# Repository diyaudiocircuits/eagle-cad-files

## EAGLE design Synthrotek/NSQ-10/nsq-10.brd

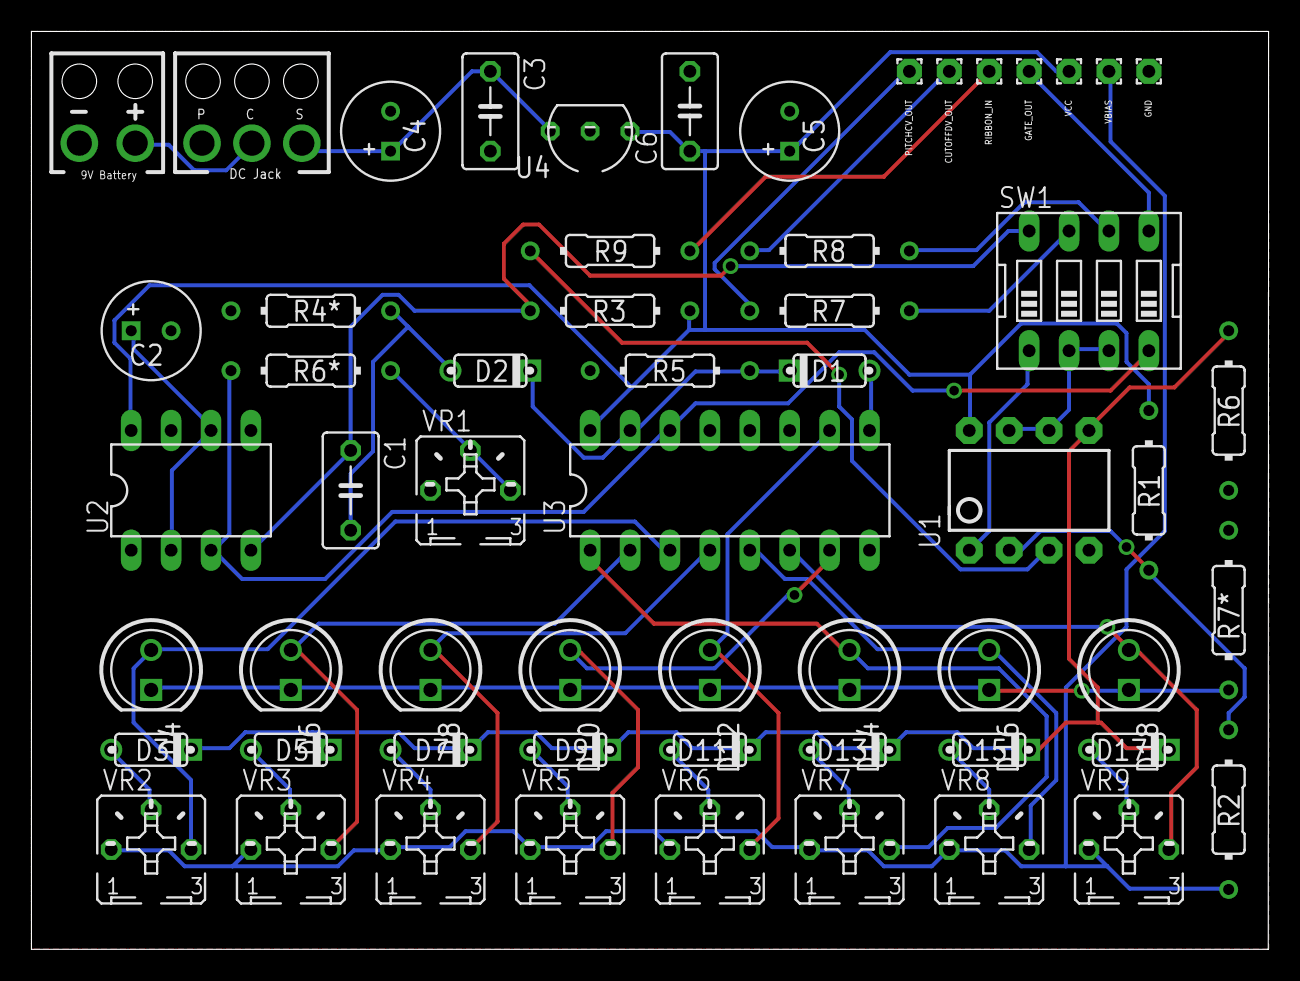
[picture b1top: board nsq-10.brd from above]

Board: 2 copper layers, 78.7 x 58.4 mm, 58 parts (0 on the bottom side), 40 nets.

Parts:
C1: 0.001uF; CERAMIC_CAP
C2: 0.47uF; 063_025
C3, C6: 0.1uF; CERAMIC_CAP
C4: 100uF; 063_025
C5: 10uF; 063_025
CUTOFFDV_OUT: 1,6/0,8
D1, D2: 1N914.2; DO35-2
D3, D5, D7, D9, D11, D13, D15, D17: 1N4148; DO35-2
D4, D6, D8, D10, D12, D14, D16, D18: LED5MM
GATE_OUT: 1,6/0,8
GND: 1,6/0,8
PITCHCV_OUT: 1,6/0,8
R1, R3, R4*, R5: 100k; RESISTOR
R2: 2.2k; RESISTOR
R6, R7*: 10k; RESISTOR
R6*: 20k; RESISTOR
R7: 91K; RESISTOR
R8: 470k; RESISTOR
R9: 1k; RESISTOR
RIBBON_IN: 1,6/0,8
SW1: EDG-04
U1: LM358; DIP08
U2: ICM7555; DIL08
U3: 4017N; DIL16
U4: 78L05ACZ; TO-92
U$1: 9V_BATTERY_CLIP; 9V_BATTERY
U$2: DC_JACK_OFFBOARD
VBIAS: 1,6/0,8
VCC: 1,6/0,8
VR1: 1M; B25P
VR2, VR3, VR4, VR5, VR6, VR7, VR8, VR9: 10k; B25P

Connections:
CLOCK: R6*.1, SW1.4, U2.3, U3.14
CUTOFFCV_B: R8.2, SW1.6
GATE_B: GATE_OUT.1, SW1.5
GND: C2.-, C3.2, C4.-, C5.-, C6.2, GND.1, R4*.1, R5.1, R6.1, R7*.1, U1.4, U2.1, U3.8, U3.13, U4.2, U$1.9V_BATTERY_-, U$2.PIN, VR1.A
unnamed: C1.2, D2.A, R4*.2
unnamed: R1.1, R2.2, U1.2
unnamed: R6*.2, VR1.E, VR1.S
unnamed: C2.+, U2.2, U2.6
unnamed: SW1.2, SW1.3, U1.6, U1.7
unnamed: D3.A, VR2.S
unnamed: R9.1, RIBBON_IN.1
unnamed: D5.A, VR3.S
unnamed: D1.A, U3.9
unnamed: D1.C, D2.C, R5.2, U3.15
unnamed: CUTOFFDV_OUT.1, R8.1
unnamed: D7.A, VR4.S
unnamed: PITCHCV_OUT.1, R7.1
unnamed: D9.A, VR5.S
unnamed: D11.A, VR6.S
unnamed: D13.A, VR7.S
unnamed: U$1.9V_BATTERY_+, U$2.CONNECT
unnamed: D15.A, VR8.S
unnamed: C3.1, C4.+, U4.3, U$2.SLEEVE
unnamed: D17.A, VR9.S
unnamed: D4.K, D6.K, D8.K, D10.K, D12.K, D14.K, D16.K, D18.K, R7*.2
unnamed: D3.C, D5.C, D7.C, D9.C, D11.C, D13.C, D15.C, D17.C, R6.2, U1.5
PITCHCV_B: R7.2, SW1.7
Q0: D4.A, U3.3, VR2.E
Q1: D6.A, U3.2, VR3.E
Q2: D8.A, U3.4, VR4.E
Q3: D10.A, U3.7, VR5.E
Q4: D12.A, U3.10, VR6.E
Q5: D14.A, U3.1, VR7.E
Q6: D16.A, U3.5, VR8.E
Q7: D18.A, U3.6, VR9.E
RESETMODE_A: SW1.1, U1.1
RESETMODE_B: C1.1, R3.1, SW1.8, U2.4
RIBBON_IN: R9.2, U1.3
VBIAS: R2.1, VBIAS.1, VR2.A, VR3.A, VR4.A, VR5.A, VR6.A, VR7.A, VR8.A, VR9.A
VCC: C5.+, C6.1, R1.2, R3.2, U1.8, U2.8, U3.16, U4.1, VCC.1

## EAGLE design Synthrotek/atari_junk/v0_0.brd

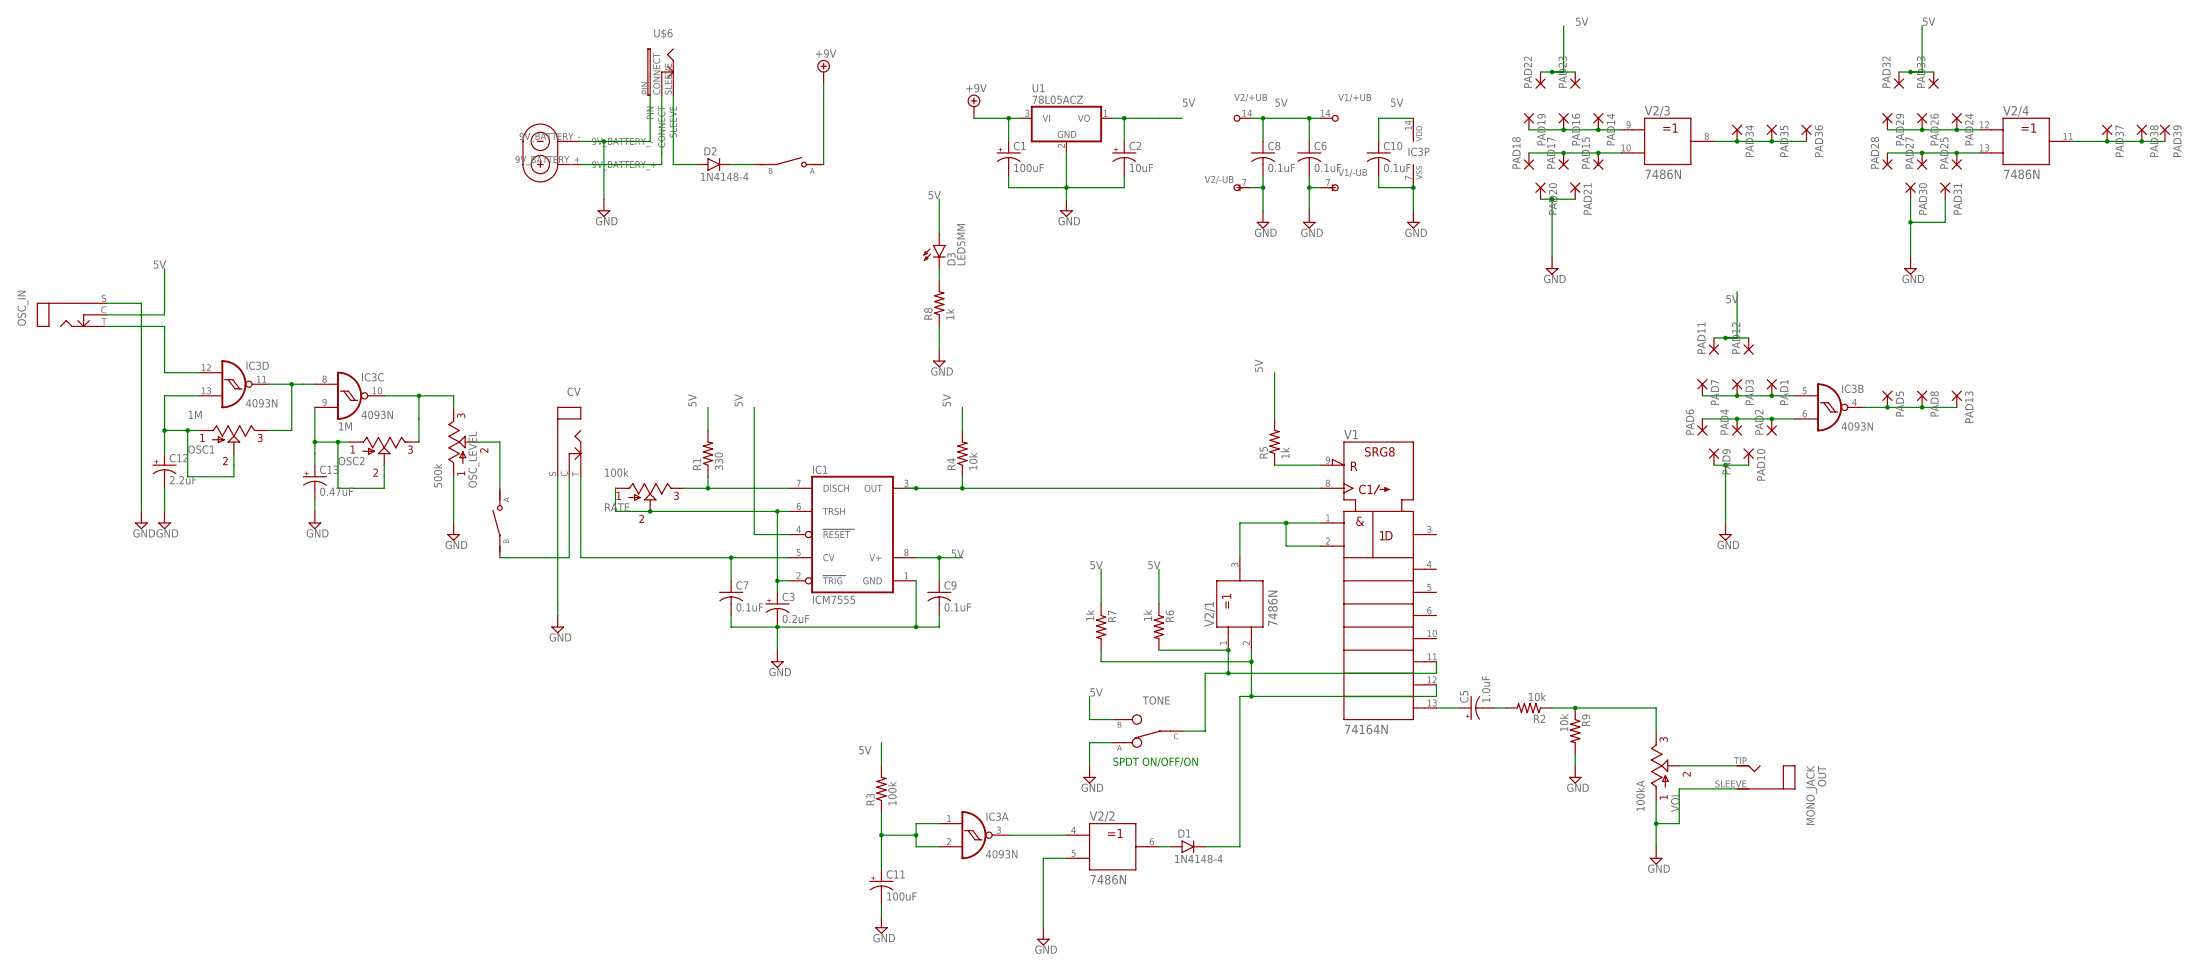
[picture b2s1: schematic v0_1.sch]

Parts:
C1, C11: 100uF; 063_025
C2: 10uF; 063_025
C3: 0.2uF; 063_025
C5: 1.0uF; 063_025
C6, C7, C8, C9, C10: 0.1uF; C050-030X075
C12: 2.2uF; 063_025
C13: 0.47uF; 063_025
CV: MONO_JACK_W_SHUNT
CV+OSC_ON/OFF: SPST_SWITCH; SPST_TOGGLE_SWITCH
D1, D2: 1N4148-4; DO35-4
D3: LED5MM
IC1: ICM7555; DIL08
IC3: 4093N; DIL14
ON/OFF: SPST_SWITCH; SPST_TOGGLE_SWITCH
OSC1, OSC2: 1M; POT
OSC_IN: MONO_JACK_W_SHUNT
OSC_LEVEL: 500k; POT
OUT: MONO_JACK
PAD1, PAD2, PAD3, PAD4, PAD5, PAD6, PAD7, PAD8, PAD9, PAD10, PAD11, PAD12, PAD13, PAD14, PAD15, PAD16, PAD17, PAD18, PAD19, PAD20, PAD21, PAD22, PAD23, PAD24, PAD25, PAD26, PAD27, PAD28, PAD29, PAD30, PAD31, PAD32, PAD33, PAD34, PAD35, PAD36, PAD37, PAD38, PAD39: WIREPAD1,6/0,9; 1,6/0,9
R1: 330; R0207/4
R2, R4, R9: 10k; R0207/4
R3: 100k; R0207/4
R5, R6, R7, R8: 1k; R0207/4
RATE: 100k; POT
TONE: SPDT_SWITCH; SPDT_TOGGLE_SWITCH
U1: 78L05ACZ; TO-92
U$6: DC_JACK_OFFBOARD
U$7: 9V_BATTERY_CLIP; 9V_BATTERY
V1: 74164N; DIL14
V2: 7486N; DIL14
VOL: 100kA; POT

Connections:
5V: C2.+, C6.1, C8.1, C9.1, C10.1, D3.A, IC1.4 (RESET), IC1.8 (V+), IC3.14 (VDD), OSC_IN.C (CONNECT), PAD11.1, PAD12.1, PAD22.1, PAD23.1, PAD32.1, PAD33.1, R1.2, R3.2, R4.2, R5.2, R6.1, R7.1, TONE.B, U1.1 (VO), V1.14 (+UB), V2.14 (+UB)
+9V: C1.+, ON/OFF.A, U1.3 (VI)
GND: C1.-, C2.-, C3.-, C6.2, C7.2, C8.2, C9.2, C10.2, C11.-, C12.-, C13.-, CV.S (SLEEVE), IC1.1 (GND), IC3.7 (VSS), OSC_IN.S (SLEEVE), OSC_LEVEL.1, OUT.SLEEVE, PAD9.1, PAD10.1, PAD20.1, PAD21.1, PAD30.1, PAD31.1, R8.1, R9.2, TONE.A, U1.2 (GND), U$6.PIN, U$7.9V_BATTERY_-, V1.7 (-UB), V2.5 (B), V2.7 (-UB), VOL.1
unnamed: C3.+, IC1.2 (TRIG), IC1.6 (TRSH), RATE.1, RATE.2
unnamed: U$6.CONNECT, U$7.9V_BATTERY_+
unnamed: IC1.3 (OUT), R4.1, V1.8 (CLK)
unnamed: IC1.7 (DISCH), R1.1, RATE.3
unnamed: R5.1, V1.9 (!CLR)
unnamed: PAD15.1, PAD17.1, PAD18.1, V2.10 (B)
unnamed: C7.1, CV.T (TIP), IC1.5 (CV)
unnamed: V1.1 (A), V1.2 (B), V2.3 (Y)
unnamed: R6.2, TONE.C, V1.11 (QF), V2.1 (A)
unnamed: D1.C, R7.2, V1.12 (QG), V2.2 (B)
unnamed: C5.+, V1.13 (QH)
unnamed: C5.-, R2.2
unnamed: R2.1, R9.1, VOL.3
unnamed: OUT.TIP, VOL.2
unnamed: IC3.12 (I0), OSC_IN.T (TIP)
unnamed: C12.+, IC3.13 (I1), OSC1.1, OSC1.2
unnamed: CV.C (CONNECT), CV+OSC_ON/OFF.B
unnamed: C11.+, IC3.1 (I0), IC3.2 (I1), R3.1
unnamed: IC3.3 (O), V2.4 (A)
unnamed: D1.A, V2.6 (Y)
unnamed: IC3.8 (I0), IC3.11 (O), OSC1.3
unnamed: D3.K (C), R8.2
unnamed: PAD14.1, PAD16.1, PAD19.1, V2.9 (A)
unnamed: IC3.4 (O), PAD5.1, PAD8.1, PAD13.1
unnamed: IC3.6 (I1), PAD2.1, PAD4.1, PAD6.1
unnamed: IC3.5 (I0), PAD1.1, PAD3.1, PAD7.1
unnamed: PAD34.1, PAD35.1, PAD36.1, V2.8 (Y)
unnamed: PAD37.1, PAD38.1, PAD39.1, V2.11 (Y)
unnamed: PAD25.1, PAD27.1, PAD28.1, V2.13 (B)
unnamed: PAD24.1, PAD26.1, PAD29.1, V2.12 (A)
unnamed: CV+OSC_ON/OFF.A, OSC_LEVEL.2
unnamed: C13.+, IC3.9 (I1), OSC2.1, OSC2.2
unnamed: D2.A, U$6.SLEEVE
unnamed: D2.C, ON/OFF.B
unnamed: IC3.10 (O), OSC2.3, OSC_LEVEL.3

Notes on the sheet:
SPDT ON/OFF/ON

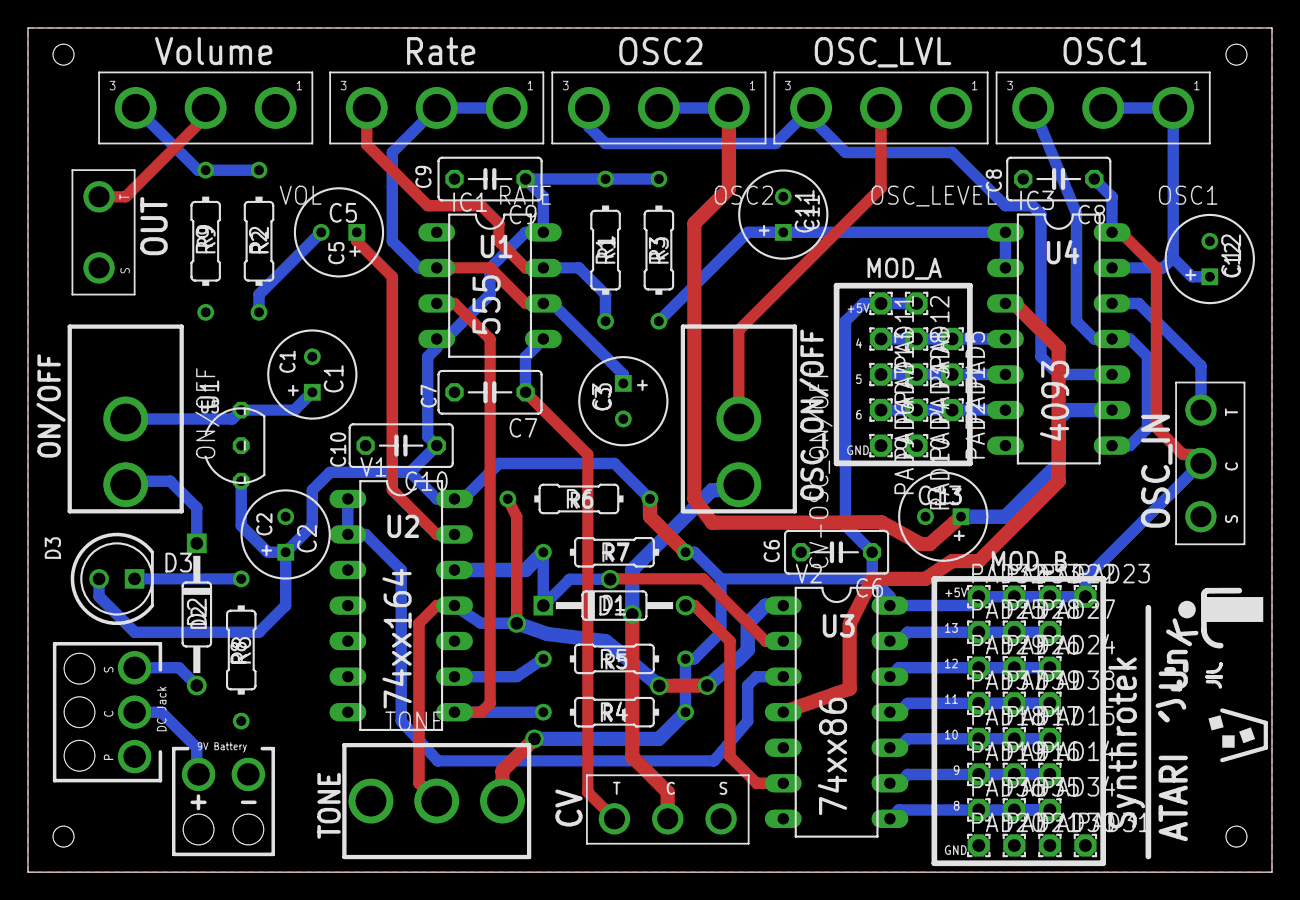
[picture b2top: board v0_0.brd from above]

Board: 2 copper layers, 88.9 x 60.3 mm, 81 parts (0 on the bottom side), 38 nets.

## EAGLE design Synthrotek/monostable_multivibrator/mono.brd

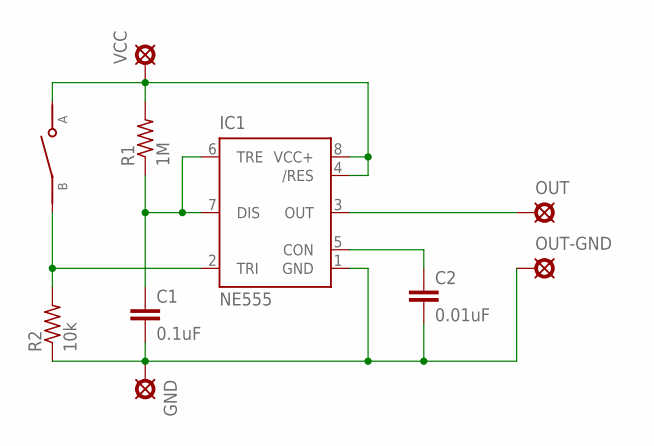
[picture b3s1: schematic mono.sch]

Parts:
C1: 0.1uF; 050X030_025
C2: 0.01uF; 050X030_025
GND: PAD8; OCTOGON
IC1: NE555; DIL-08
OUT: PAD; SQUARE
OUT-GND: PAD; SQUARE
R1: 1M; R0207/4
R2: 10k; R0207/4
SW1: SPST_SWITCH; SPST_TOGGLE_SWITCH
VCC: PAD; SQUARE

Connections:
unnamed: C1.1, IC1.6 (TRE), IC1.7 (DIS), R1.1
unnamed: IC1.3 (OUT), OUT.1
unnamed: IC1.4 (/RES), IC1.8 (VCC+), R1.2, SW1.A, VCC.1
unnamed: IC1.2 (TRI), R2.2, SW1.B
unnamed: C2.1, IC1.5 (CON)
unnamed: C1.2, C2.2, GND.1, IC1.1 (GND), OUT-GND.1, R2.1

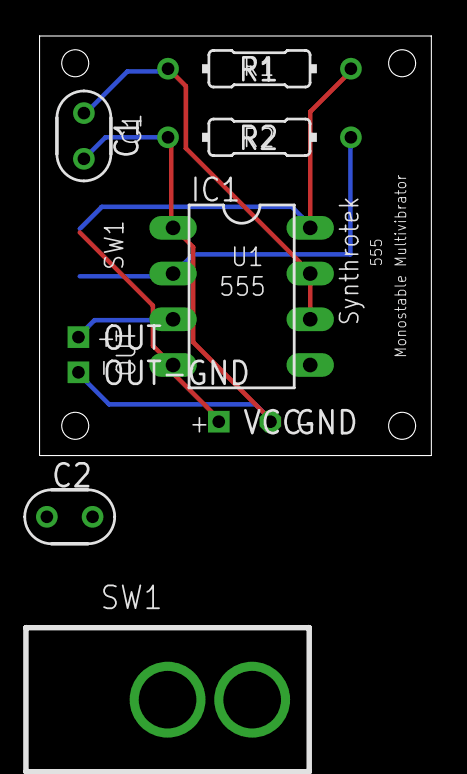
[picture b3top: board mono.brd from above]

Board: 2 copper layers, 21.8 x 23.3 mm, 10 parts (0 on the bottom side), 6 nets.
